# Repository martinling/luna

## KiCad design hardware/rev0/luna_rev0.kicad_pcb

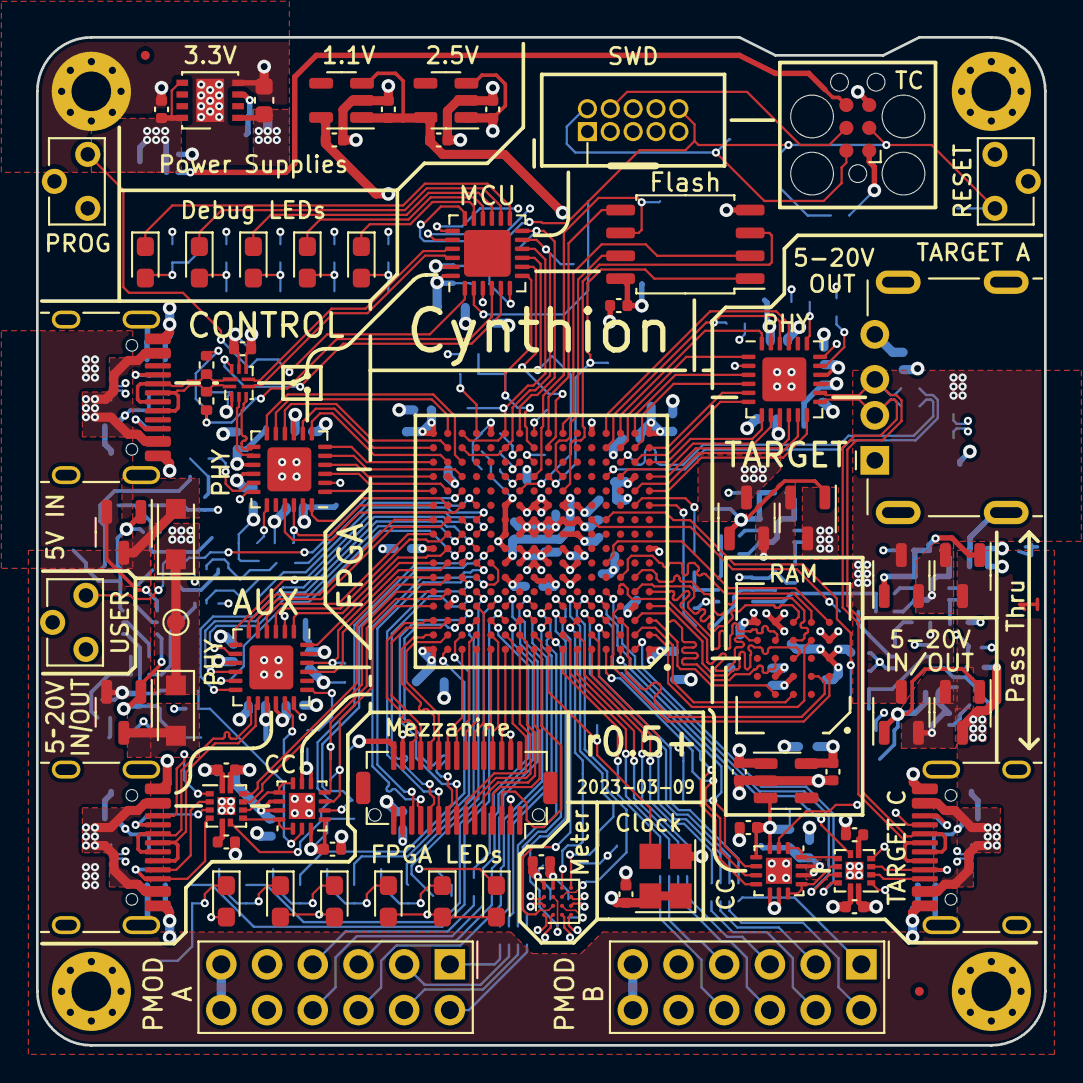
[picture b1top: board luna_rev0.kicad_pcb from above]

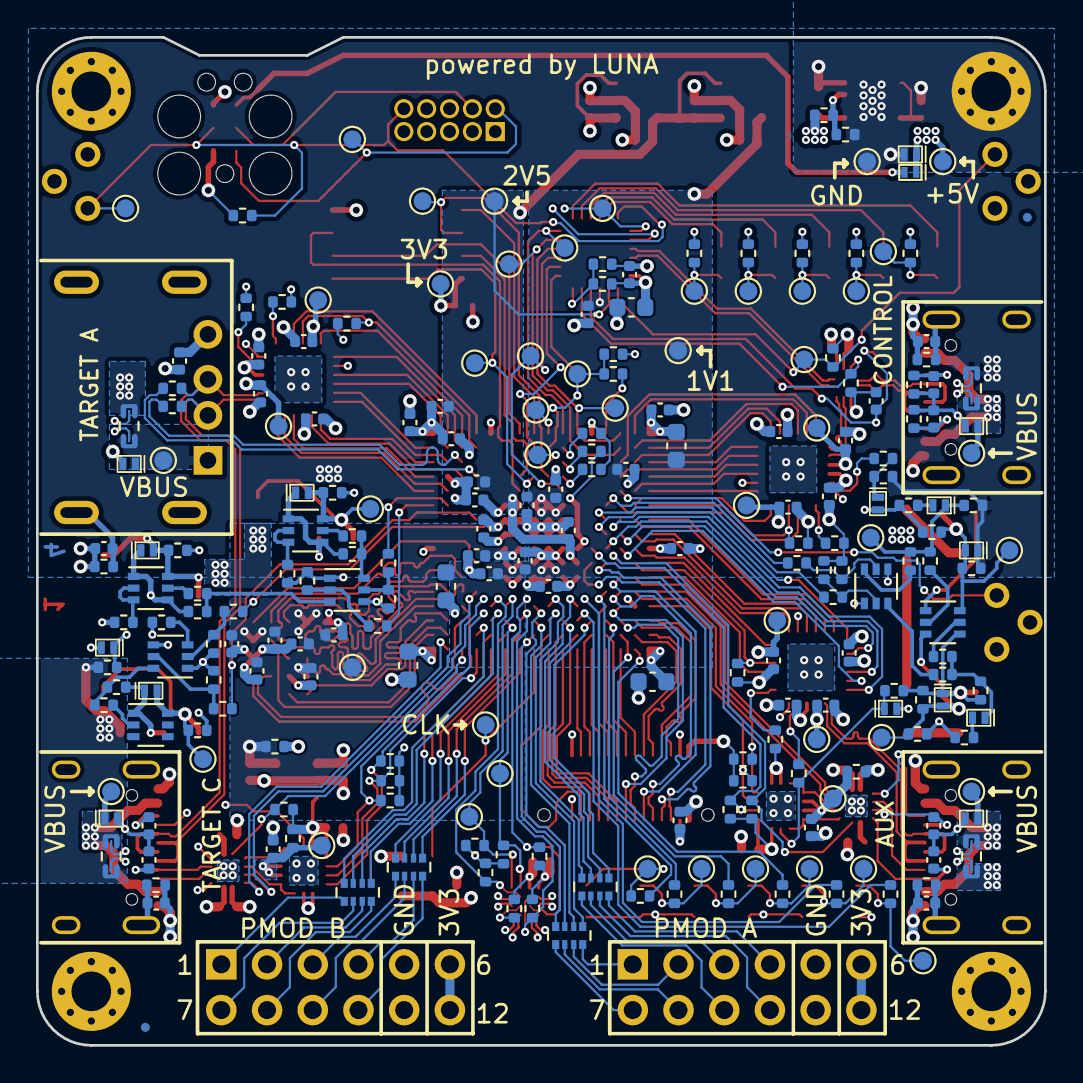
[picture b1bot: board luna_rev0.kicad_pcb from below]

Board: 4 copper layers, 56.0 x 56.0 mm, 313 parts (235 on the bottom side), 285 nets.

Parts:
C1, C2, C3, C4, C20, C73: 2.2uF; C_0603_1608Metric
C5, C6, C8, C13, C16, C17, C18, C19, C21, C22, C28, C29, C30, C34, C36, C37, C41, C42, C43, C48, C49, C50, C56, C58, C59, C60, C72, C74: 1uF; C_0402_1005Metric
C7, C9, C10, C11, C12, C14, C15, C23, C24, C26, C27, C31, C32, C33, C35, C38, C39, C40, C44, C45, C46, C51, C57, C61, C63, C64, C65, C66, C67, C68, C69, C70, C71: 0.1uF; C_0402_1005Metric
C25, C47, C52, C53, C54, C55: 390pF; C_0402_1005Metric
C62: 1nF; C_0402_1005Metric
D1, D8: D; D_SOD-123F
D2: RED; LED_0603_1608Metric_Pad1.05x0.95mm_HandSolder
D3: ORANGE; LED_0603_1608Metric_Pad1.05x0.95mm_HandSolder
D4: YELLOW; LED_0603_1608Metric_Pad1.05x0.95mm_HandSolder
D5: GREEN; LED_0603_1608Metric_Pad1.05x0.95mm_HandSolder
D6: BLUE; LED_0603_1608Metric_Pad1.05x0.95mm_HandSolder
D7: PURPLE; LED_0603_1608Metric_Pad1.05x0.95mm_HandSolder
D9: PMEG4010ESBYL; DSN1006-2
D10, D14: ICE BLUE; LED_0603_1608Metric_Pad1.05x0.95mm_HandSolder
D11, D13: PINK; LED_0603_1608Metric_Pad1.05x0.95mm_HandSolder
D12: WHITE; LED_0603_1608Metric_Pad1.05x0.95mm_HandSolder
D15, D18, D22: 24±2%; DFN1006-2
D16, D20: 18±2%; DFN1006-2
D17, D21: 5.6±2%; DFN1006-2
D19, D27, D28, D29: 6.2±2%; DFN1006-2
D23, D24, D25, D26: TVS; DFN1006-2
FID1, FID2, FID3, FID4: Fiducial; Fiducial_0.5mm_Mask1mm
H1, H2, H3, H4: MountingHole; MountingHole_2.2mm_M2_Pad_Via
IC1: ECP5-BGA256; lattice_cabga256
J1, J2, J4: USB_C_Receptacle_USB2.0; USB_C_Receptacle_HRO_TYPE-C-31-M-12
J3: USB_A; USB_A_Kycon_KUSBXHT-SB-AS1N-B30-NF_Horizontal
J5: MEZZANINE; Amphenol_10132798-03
J6: MCU_SWD; SWD_CONNECTOR_LARGE_BOX
J7: PMOD_A; PinSocket_2x06_P2.54mm_PMOD
J8: PMOD_B; PinSocket_2x06_P2.54mm_PMOD
J10: TC_SWD; Tag-Connect_TC2030-IDC-FP_2x03_P1.27mm_Vertical
Q1, Q2, Q4, Q5, Q6, Q7, Q9, Q12: PMOS; SOT-23-3
Q3, Q8, Q11: 2NPN; SOT-363_SC-70-6
Q10, Q13, Q14, Q15: 2PNP; SOT-363_SC-70-6
R1, R2, R42, R59: 0.02±1%; R_0603_1608Metric_Current_Sense
R3, R47, R48, R49, R60, R61, R69, R70, R76, R77: 33k; R_0402_1005Metric
R4, R32, R36, R43, R50, R51, R54, R102: 0; R_0402_1005Metric
R5, R8, R9, R10, R30, R31, R33, R38, R40, R63, R65, R71, R78, R83, R84, R88, R97, R98: 2.2k; R_0402_1005Metric
R6, R12, R13, R14, R15, R22, R23, R24, R25, R29, R37, R39, R41, R52, R53, R64, R66, R72, R79, R85, R86, R87, R89, R99, R100, R101: 10k; R_0402_1005Metric
R7, R11, R34, R35, R44, R45, R46: 5.1k; R_0402_1005Metric
R16, R18, R20: 8.06k±1%; R_0402_1005Metric
R17, R19, R21: 20k; R_0402_1005Metric
R26, R27, R28, R57, R58: 1k; R_0402_1005Metric
R55, R56, R68, R75: 820k; R_0402_1005Metric
R62, R90, R91, R92, R93, R94, R95, R96: 100k; R_0402_1005Metric
R67, R73, R74, R80, R82: 18.7k±1%; R_0402_1005Metric
R81: 58.3k±1%; R_0402_1005Metric
RN1, RN2, RN3, RN4: 33; R_Array_Convex_4x0402
SW1: BTN_PROGRAM; SW_Tactile_SPST_Angled_TC-1109DE-B-F
SW2: BTN_RESET; SW_Tactile_SPST_Angled_TC-1109DE-B-F
SW3: BTN_USER; SW_Tactile_SPST_Angled_TC-1109DE-B-F
TP1, TP2, TP3, TP4, TP5, TP6, TP7, TP8, TP9, TP10, TP11, TP12, TP13, TP14, TP15, TP16, TP17, TP18, TP19, TP20, TP21, TP22, TP23, TP24, TP26, TP27, TP28, TP29, TP30, TP31, TP32, TP34, TP35, TP36, TP37, TP38, TP39, TP40, TP41, TP42, TP43, TP44, TP46, TP47, TP49, TP50, TP51, TP52, TP53, TP54, TP55: TestPoint; TestPoint_Pad_D1.0mm
U1: PAC195X-1-WLCSP; WLCSP-16_2.225x2.170mm_Layout4x4_P0.5mm
U2, U12: FUSB302BMPX; WQFN-14-1EP_2.5x2.5mm_P0.5mm_EP1.45x1.45mm
U3: AP7361EA-33; DFN-8-1EP_3x3mm_P0.65mm_EP1.55x2.4mm
U4: TCR2EF115; SOT-23-5
U5: MIC5504-2.5YM5; SOT-23-5
U6: ATSAMD11; QFN-24-1EP_4x4mm_P0.5mm_EP2.6x2.6mm
U7: W25Q32JVSS; SOIC-8_5.23x5.23mm_P1.27mm
U8, U9, U11: USB3343-CP; VQFN-24-1EP_4x4mm_P0.5mm_EP2.45x2.45mm
U10: HyperRAM; BGA-24_5x5_6.0x8.0mm
U13, U14: DPO2036; Diodes_UQFN2020-12_Type-B
U15: MIC5504-1.8YM5; SOT-23-5
U16: PI3USB102G; Diodes_10-TQFN_ZL
Y1: Osc60MHz; Crystal_SMD_3225-4Pin_3.2x2.5mm

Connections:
+1V1: C1.1, C3.1, C7.1, C9.1, C11.1, C13.1, C15.1, C17.1, C29.1, IC1.G6 (VCC_1), IC1.G7 (VCC_2), IC1.G9 (VCC_3), IC1.L8 (VCC_4), IC1.L9 (VCC_5), IC1.L10 (VCC_6), TP4.1, U4.5 (VOUT), U6.3 (PA04)
+2V5: C22.1, C24.1, C26.1, C27.1, C30.1, IC1.G11 (VCCAUX_1), IC1.L7 (VCCAUX_2), TP5.1, U4.1 (VIN), U4.3 (EN), U5.5 (VOUT), U6.2 (PA03)
+3V3: C2.1, C4.1, C8.1, C10.1, C12.1, C14.1, C16.1, C18.1, C20.1, C23.1, C28.1, C33.1, C34.1, C35.1, C38.1, C39.1, C40.1, C41.1, C44.1, C46.1, C49.1, C56.1, C58.1, C59.1, C61.1, C66.1, C67.1, C72.1, C73.1, C74.1, D2.2 (A), D3.2 (A), D4.2 (A), D5.2 (A), D6.2 (A), D7.2 (A), IC1.F6 (VCCIO0_1), IC1.F7 (VCCIO0_2), IC1.F10 (VCCIO1_1), IC1.F11 (VCCIO1_2), IC1.H11 (VCCIO2_1), IC1.J6 (VCCIO6_1), IC1.J7 (VCCIO6_2), IC1.J11 (VCCIO2_2), IC1.K11 (VCCIO3_1), IC1.L6 (VCCIO8), IC1.L11 (VCCIO3_2), J5.15, J5.16, J6.1 (VTref), J7.6, J7.12, J8.6, J8.12, J10.1, R6.1, R7.1, R8.1, R9.1, R10.1, R11.1, R13.2, R25.1, R32.2, R33.1, R36.2, R37.1, R38.1, R39.1, R52.1, R54.1, R81.1, R83.1, R84.1, R85.1, R86.1, R87.1, R97.1, R98.1, R99.1, R100.1, R101.1, TP3.1, U1.A4 (VDD), U2.3 (VDD), U2.4 (VDD), U3.1 (OUT), U5.1 (VIN), U5.3 (EN), U6.24 (VDD), U7.8 (VCC), U8.2 (CLKOUT), U8.9 (VDDIO), U8.16 (VBAT), U8.18 (ID), U9.2 (CLKOUT), U9.9 (VDDIO), U9.16 (VBAT), U9.18 (ID), U11.2 (CLKOUT), U11.9 (VDDIO), U11.16 (VBAT), U11.18 (ID), U12.3 (VDD), U12.4 (VDD), U13.12 (VSYS), U14.12 (VSYS), U15.1 (VIN), U15.3 (EN), U16.9 (VCC), Y1.1 (EN), Y1.4 (VDD)
+5V: C6.1, D1.1 (K), D8.1 (K), D9.1 (K), D19.1 (K), TP30.1, TP49.1, U3.5 (EN), U3.8 (IN)
/AUX Port/AUX.CLK: IC1.F16 (PR14A), U11.21 (REFCLK/XI)
/AUX Port/AUX.DATA0: IC1.J16 (PR23A), U11.4 (DATA0)
/AUX Port/AUX.DATA1: IC1.K15 (PR23D), U11.5 (DATA1)
/AUX Port/AUX.DATA2: IC1.K16 (PR23C), U11.6 (DATA2)
/AUX Port/AUX.DATA3: IC1.J13 (PR17C), U11.7 (DATA3)
/AUX Port/AUX.DATA4: IC1.J14 (PR20C), U11.8 (DATA4)
/AUX Port/AUX.DATA5: IC1.H13 (PR17B), U11.10 (DATA5)
/AUX Port/AUX.DATA6: IC1.H14 (PR14D), U11.11 (DATA6)
/AUX Port/AUX.DATA7: IC1.K14 (PR20D), U11.12 (DATA7)
/AUX Port/AUX.DIR: IC1.H15 (PR20B), U11.1 (DIR)
/AUX Port/AUX.NXT: IC1.J15 (PR23B), U11.3 (NXT)
/AUX Port/AUX.STP: IC1.G16 (PR20A), U11.24 (STP)
/AUX Port/AUX.~RESET: IC1.G15 (PR14B), R24.1, U11.22 (RESET)
/AUX Port/AUX_CC1: C52.1, J1.A5 (CC1), U14.3 (CC1C)
/AUX Port/AUX_CC1S: U12.10 (CC1), U12.11 (CC1), U14.8 (CC1S)
/AUX Port/AUX_CC2: C53.1, J1.B5 (CC2), U14.4 (CC2C)
/AUX Port/AUX_CC2S: U12.1 (CC2), U12.14 (CC2), U14.7 (CC2S)
/AUX Port/AUX_D+: J1.A6 (D+), J1.B6 (D+), U11.14 (D+)
/AUX Port/AUX_D-: J1.A7 (D-), J1.B7 (D-), U11.13 (D-)
/AUX Port/AUX_PHY_1V8: C50.1, TP35.1, U11.23 (VDD18)
/AUX Port/AUX_SBU1: J1.A8 (SBU1), U14.2 (SBU2C)
/AUX Port/AUX_SBU1S: IC1.F15 (PR11C), U14.10 (SBU1S)
/AUX Port/AUX_SBU2: J1.B8 (SBU2), U14.1 (SBU1C)
/AUX Port/AUX_SBU2S: IC1.E16 (PR11D), U14.9 (SBU2S)
/AUX Port/AUX_SCL: IC1.D16 (PR8A), R38.2, U12.6 (SCL)
/AUX Port/AUX_SDA: IC1.E15 (PR8B), R33.2, U12.7 (SDA)
/AUX Port/AUX_VCONN: C51.1, R32.1, TP37.1, U12.12 (VCONN), U12.13 (VCONN)
/AUX Port/~AUX_FAULT: IC1.G14 (PR14C), R99.2, U14.6 (FAULTB)
/AUX Port/~AUX_INT: IC1.H12 (PR17A), R39.2, U12.5 (INT_N)
/CONTROL Port/CONTROL.CLK: IC1.L14 (PR32C), U8.21 (REFCLK/XI)
/CONTROL Port/CONTROL.DATA0: IC1.N16 (PR32A), U8.4 (DATA0)
/CONTROL Port/CONTROL.DATA1: IC1.N14 (PR35D), U8.5 (DATA1)
/CONTROL Port/CONTROL.DATA2: IC1.P16 (PR35A), U8.6 (DATA2)
/CONTROL Port/CONTROL.DATA3: IC1.P15 (PR32B), U8.7 (DATA3)
/CONTROL Port/CONTROL.DATA4: IC1.R16 (PR35B), U8.8 (DATA4)
/CONTROL Port/CONTROL.DATA5: IC1.R15 (PR38C), U8.10 (DATA5)
/CONTROL Port/CONTROL.DATA6: IC1.T15 (PR38D), U8.11 (DATA6)
/CONTROL Port/CONTROL.DATA7: IC1.P14 (PR38B), U8.12 (DATA7)
/CONTROL Port/CONTROL.DIR: IC1.M16 (PR26C), U8.1 (DIR)
/CONTROL Port/CONTROL.NXT: IC1.M15 (PR26D), U8.3 (NXT)
/CONTROL Port/CONTROL.STP: IC1.L15 (PR26B), U8.24 (STP)
/CONTROL Port/CONTROL.~RESET: IC1.L16 (PR26A), R22.1, U8.22 (RESET)
/CONTROL Port/CONTROL_CC1: C25.1, J2.A5 (CC1), R34.2
/CONTROL Port/CONTROL_CC2: C47.1, J2.B5 (CC2), R35.2
/CONTROL Port/CONTROL_D+: J2.A6 (D+), J2.B6 (D+), R56.2, U16.2 (D-)
/CONTROL Port/CONTROL_D-: J2.A7 (D-), J2.B7 (D-), R55.1, U16.1 (D+)
/CONTROL Port/CONTROL_FPGA_D+: U8.14 (D+), U16.4 (1D-)
/CONTROL Port/CONTROL_FPGA_D-: U8.13 (D-), U16.5 (1D+)
/CONTROL Port/CONTROL_MCU_D+: U6.22 (PA25), U16.6 (2D-)
/CONTROL Port/CONTROL_MCU_D-: U6.21 (PA24), U16.7 (2D+)
/CONTROL Port/CONTROL_PHY_1V8: C37.1, TP17.1, U8.23 (VDD18)
/CONTROL Port/CONTROL_RESET_DETECT: C62.1, R55.2, R56.1, U6.4 (PA05)
/CONTROL Port/CONTROL_SWITCH: R15.1, U6.5 (PA06), U16.10 (S)
/CONTROL Port/CONTROL_VBUS_CLAMPED: D22.1 (K), R17.1, R46.1
/CONTROL Port/~AUX_VBUS_IN_EN: IC1.L13 (PR29C), R78.2
/CONTROL Port/~BTN_USER: IC1.M14 (PR32D), SW3.1 (A)
/CONTROL Port/~CONTROL_VBUS_IN_EN: IC1.K13 (PR29A), R71.2
/CONTROL Port/~FPGA_SELF_PROGRAM: IC1.T13 (PR44B), R5.2
/Clock and Pmod/CLKIN_60MHZ: IC1.A8 (PT29B), TP1.1, Y1.3 (OUT)
/Clock and Pmod/TARGET_C.SBU1S: IC1.A2 (PT4A), U13.10 (SBU1S)
/Clock and Pmod/TARGET_C.SBU2S: IC1.E4 (PT9A), U13.9 (SBU2S)
/Clock and Pmod/TARGET_C.SCL: IC1.A4 (PT6B), R98.2, U2.6 (SCL)
/Clock and Pmod/TARGET_C.SDA: IC1.C4 (PT11A), R97.2, U2.7 (SDA)
/Clock and Pmod/TARGET_C.~FAULT: IC1.D4 (PT9B), R100.2, U13.6 (FAULTB)
/Clock and Pmod/TARGET_C.~INT: IC1.A3 (PT6A), R37.2, U2.5 (INT_N)
/Debugger and FPGA Configuration/D0: IC1.T8 (D0/PICO/PB11B), U7.5 (DI(IO0))
/Debugger and FPGA Configuration/D1: IC1.T7 (D1/PICO/PB11A), U7.2 (DO(IO1))
/Debugger and FPGA Configuration/D2: IC1.M7 (D2/PB9B), U7.3 (IO2)
/Debugger and FPGA Configuration/D3: IC1.N7 (D3/PB9A), U7.7 (IO3)
/Debugger and FPGA Configuration/FPGA_CFG0: IC1.N10 (CFG_0), R12.1
/Debugger and FPGA Configuration/FPGA_CFG1: IC1.P10 (CFG_1), R13.1
/Debugger and FPGA Configuration/FPGA_CFG2: IC1.R10 (CFG_2), R14.1
/Debugger and FPGA Configuration/FPGA_CONFIG_CLK: IC1.N9 (MCLK/SCLK/CCLK), TP10.1, U7.6 (CLK)
/Debugger and FPGA Configuration/FPGA_DONE: IC1.P9 (DONE), TP12.1
/Debugger and FPGA Configuration/FPGA_INT: IC1.R8 (SN/CSN/PB13A), U6.8 (PA09/XOUT)
/Debugger and FPGA Configuration/FPGA_TCK: IC1.T10 (TCK), TP21.1, U6.12 (PA15)
/Debugger and FPGA Configuration/FPGA_TDI: IC1.R11 (TDI), IC1.R14 (PR41B), TP24.1, U6.11 (PA14)
/Debugger and FPGA Configuration/FPGA_TDO: IC1.M10 (TDO), TP23.1, U6.9 (PA10)
/Debugger and FPGA Configuration/FPGA_TMS: IC1.T11 (TMS), IC1.T14 (PR41D), TP22.1, U6.10 (PA11)
/Debugger and FPGA Configuration/MCU_SWDCLK: J6.4 (SWDCLK/TCK), J10.4, TP19.1, U6.19 (PA30/SWCLK)
/Debugger and FPGA Configuration/MCU_SWDIO: J6.2 (SWDIO/TMS), J10.2, TP20.1, U6.20 (PA31/SWDIO)
/Debugger and FPGA Configuration/~BTN_PROGRAM: R101.2, SW1.1 (A), TP15.1, U6.1 (PA02)
/Debugger and FPGA Configuration/~BTN_RESET: J6.10 (~RESET), J10.3, R25.2, SW2.1 (A), TP18.1, U6.18 (PA28/~RST)
/Debugger and FPGA Configuration/~CS_DI: IC1.N8 (HOLDN/DI/PB15A), TP11.1, U7.1 (~CS)
/Debugger and FPGA Configuration/~FPGA_INIT: IC1.T9 (INITN), TP13.1
/Debugger and FPGA Configuration/~FPGA_PROGRAM: IC1.R9 (PROGRAMN), R5.1, R6.2, TP14.1, U6.7 (PA08/XIN)
/LEDs and Pmod/LED0: IC1.E13 (PT62B), R31.2
/LEDs and Pmod/LED1: IC1.C13 (PT60B), R30.2
/LEDs and Pmod/LED2: IC1.B14 (PT67A), R29.2
/LEDs and Pmod/LED3: IC1.A15 (PT67B), R28.2
/LEDs and Pmod/LED4: IC1.D12 (PT58A), R27.2
/LEDs and Pmod/LED5: IC1.C11 (PT49B), R26.2
/PMOD_A0: J7.1, RN1.8 (R1.2)
/PMOD_A1: J7.2, RN1.7 (R2.2)
/PMOD_A2: J7.3, RN2.6 (R3.2)
/PMOD_A3: J7.4, RN2.8 (R1.2)
/PMOD_A4: J7.7, RN1.5 (R4.2)
/PMOD_A5: J7.8, RN1.6 (R3.2)
/PMOD_A6: J7.9, RN2.5 (R4.2)
/PMOD_A7: J7.10, RN2.7 (R2.2)
/PMOD_B0: J8.1, RN4.5 (R4.2)
/PMOD_B1: J8.2, RN4.7 (R2.2)
/PMOD_B2: J8.3, RN3.5 (R4.2)
/PMOD_B3: J8.4, RN3.7 (R2.2)
/PMOD_B4: J8.7, RN4.6 (R3.2)
/PMOD_B5: J8.8, RN4.8 (R1.2)
/PMOD_B6: J8.9, RN3.6 (R3.2)
/PMOD_B7: J8.10, RN3.8 (R1.2)
/Power Distribution and Monitoring/ADDRSEL: R102.2, U1.C2 (ADDRSEL)
/Power Distribution and Monitoring/AUX_VBUS: D25.1 (K), J1.A4 (VBUS), J1.A9 (VBUS), J1.B4 (VBUS), J1.B9 (VBUS), R42.4, TP34.1
/Power Distribution and Monitoring/AUX_VBUS_EN: IC1.L2 (PL26B), R63.2
/Power Distribution and Monitoring/CONTROL_VBUS: D23.1 (K), J2.A4 (VBUS), J2.A9 (VBUS), J2.B4 (VBUS), J2.B9 (VBUS), R1.1, TP16.1
/Power Distribution and Monitoring/CONTROL_VBUS_EN: IC1.L1 (PL26A), R40.2
/Power Distribution and Monitoring/TARGET_A_DISCHARGE: IC1.K4 (PL29A), R88.2
/Power Distribution and Monitoring/TARGET_A_VBUS: D24.1 (K), J3.1 (VBUS), R2.4, TP7.1
/Power Distribution and Monitoring/TARGET_C_VBUS: D26.1 (K), J4.A4 (VBUS), J4.A9 (VBUS), J4.B4 (VBUS), J4.B9 (VBUS), R59.4, TP40.1
/Power Distribution and Monitoring/~TARGET_C_VBUS_EN: IC1.K5 (PL29B), R65.2
/RAM/RAM.CK: IC1.C3 (PL2C), U10.B2 (CK)
/RAM/RAM.DQ0: IC1.F2 (PL11C), U10.D3 (DQ0)
/RAM/RAM.DQ1: IC1.B1 (PL2A), U10.D2 (DQ1)
/RAM/RAM.DQ2: IC1.C2 (PL5B), U10.C4 (DQ2)
/RAM/RAM.DQ3: IC1.E1 (PL11D), U10.D4 (DQ3)
/RAM/RAM.DQ4: IC1.E3 (PL5C), U10.D5 (DQ4)
/RAM/RAM.DQ5: IC1.E2 (PL8B), U10.E3 (DQ5)
/RAM/RAM.DQ6: IC1.F3 (PL5D), U10.E2 (DQ6)
/RAM/RAM.DQ7: IC1.G4 (PL11B), U10.E1 (DQ7)
/RAM/RAM.RWDS: IC1.D1 (PL8A), U10.C3 (RWDS)
/RAM/RAM.~CK: IC1.D3 (PL2D), U10.B1 (~CK)
/RAM/RAM.~CS: IC1.B2 (PL2B), U10.A3 (~CS)
/RAM/RAM.~RESET: IC1.C1 (PL5A), U10.A4 (~RESET)
/TARGET Port/TARGET.CLK: IC1.T4 (PL44B), U9.21 (REFCLK/XI)
/TARGET Port/TARGET.DATA0: IC1.R2 (PL38C), U9.4 (DATA0)
/TARGET Port/TARGET.DATA1: IC1.R1 (PL35B), U9.5 (DATA1)
/TARGET Port/TARGET.DATA2: IC1.P2 (PL32B), U9.6 (DATA2)
/TARGET Port/TARGET.DATA3: IC1.P1 (PL35A), U9.7 (DATA3)
/TARGET Port/TARGET.DATA4: IC1.N3 (PL35D), U9.8 (DATA4)
/TARGET Port/TARGET.DATA5: IC1.N1 (PL32A), U9.10 (DATA5)
/TARGET Port/TARGET.DATA6: IC1.M2 (PL26D), U9.11 (DATA6)
/TARGET Port/TARGET.DATA7: IC1.M1 (PL26C), U9.12 (DATA7)
/TARGET Port/TARGET.DIR: IC1.R3 (PL41B), U9.1 (DIR)
/TARGET Port/TARGET.NXT: IC1.T2 (PL38D), U9.3 (NXT)
/TARGET Port/TARGET.STP: IC1.T3 (PL41D), U9.24 (STP)
/TARGET Port/TARGET.~RESET: IC1.R4 (PL41C), R23.1, U9.22 (RESET)
/TARGET Port/TARGET_CC1: C54.1, J4.A5 (CC1), U13.3 (CC1C)
/TARGET Port/TARGET_CC1S: U2.10 (CC1), U2.11 (CC1), U13.8 (CC1S)
/TARGET Port/TARGET_CC2: C55.1, J4.B5 (CC2), U13.4 (CC2C)
/TARGET Port/TARGET_CC2S: U2.1 (CC2), U2.14 (CC2), U13.7 (CC2S)
/TARGET Port/TARGET_D+: J3.3 (D+), J4.A6 (D+), J4.B6 (D+), R58.1, U9.14 (D+)
/TARGET Port/TARGET_D-: J3.2 (D-), J4.A7 (D-), J4.B7 (D-), R57.1, U9.13 (D-)
/TARGET Port/TARGET_FS_MONITOR_D+: IC1.N4 (PL38A), R58.2
/TARGET Port/TARGET_FS_MONITOR_D-: IC1.P3 (PL38B), R57.2
/TARGET Port/TARGET_PHY_1V8: C43.1, TP27.1, U9.23 (VDD18)
/TARGET Port/TARGET_SBU1: J4.A8 (SBU1), U13.1 (SBU1C)
/TARGET Port/TARGET_SBU2: J4.B8 (SBU2), U13.2 (SBU2C)
/TARGET Port/TARGET_VCONN: C45.1, R36.1, TP36.1, U2.12 (VCONN), U2.13 (VCONN)
AUX_SENSE+: R42.3, U1.A3 (SENSE1+)
AUX_SENSE-: R42.2, U1.A2 (SENSE1-)
AUX_VBUS_CLAMPED: D15.1 (K), R21.1, R44.1, U12.2 (VBUS)
AUX_VBUS_IN: D20.1 (K), Q4.3 (D), Q10.4 (E2), Q12.2 (S), R42.1, R44.2, R74.1, R75.1
CONTROL_SENSE+: R1.2, U1.A1 (SENSE2+)
CONTROL_SENSE-: R1.3, U1.B1 (SENSE2-)
CONTROL_VBUS_IN: D16.1 (K), Q1.3 (D), Q9.2 (S), Q10.1 (E1), R1.4, R46.2, R67.1, R68.1
GND: C1.2, C2.2, C3.2, C4.2, C5.2, C6.2, C7.2, C8.2, C9.2, C10.2, C11.2, C12.2, C13.2, C14.2, C15.2, C16.2, C17.2, C18.2, C19.2, C20.2, C21.2, C22.2, C23.2, C24.2, C25.2, C26.2, C27.2, C28.2, C29.2, C30.2, C31.2, C32.2, C33.2, C34.2, C35.2, C36.2, C37.2, C38.2, C39.2, C40.2, C41.2, C42.2, C43.2, C44.2, C45.2, C46.2, C47.2, C48.2, C49.2, C50.2, C51.2, C52.2, C53.2, C54.2, C55.2, C56.2, C57.2, C58.2, C59.2, C60.2, C61.2, C62.2, C63.2, C64.2, C65.2, C66.2, C67.2, C68.2, C69.1, C70.2, C71.1, C72.2, C73.2, C74.2, D15.2 (A), D18.2 (A), D19.2 (A), D22.2 (A), D23.2 (A), D24.2 (A), D25.2 (A), D26.2 (A), H1.1, H2.1, H3.1, H4.1, IC1.A1 (GND_1), IC1.A16 (GND_2), IC1.D2 (GND_3), IC1.D15 (GND_4), IC1.F8 (GND_5), IC1.F9 (GND_6), IC1.G8 (GND_7), IC1.G10 (GND_8), IC1.H1 (GND_9), IC1.H8 (GND_10), IC1.H9 (GND_11), IC1.H10 (GND_12), IC1.H16 (GND_13), IC1.J8 (GND_14), IC1.J9 (GND_15), IC1.J10 (GND_16), IC1.K6 (GND_17), IC1.K7 (GND_18), IC1.K8 (GND_19), IC1.K9 (GND_20), IC1.K10 (GND_21), IC1.N2 (GND_22), IC1.N15 (GND_23), IC1.T1 (GND_24), IC1.T5 (GND_25), IC1.T12 (GND_26), IC1.T16 (GND_27), J1.A1 (GND), J1.A12 (GND), J1.B1 (GND), J1.B12 (GND), J2.A1 (GND), J2.A12 (GND), J2.B1 (GND), J2.B12 (GND), J3.4 (GND), J4.A1 (GND), J4.A12 (GND), J4.B1 (GND), J4.B12 (GND), J5.2, J5.14, J5.17, J5.29, J6.3 (GND), J6.5 (GND), J6.9 (GNDDetect), J7.5, J7.11, J8.5, J8.11, J10.5, Q3.1 (E1), Q3.4 (E2), Q8.1 (E1), Q8.4 (E2), Q11.1 (E1), Q11.4 (E2), R4.1, R12.2, R14.2, R15.2, R16.1, R18.1, R20.1, R22.2, R23.2, R24.2, R34.1, R35.1, R41.2, R43.2, R50.1, R51.2, R53.2, R64.2, R66.2, R70.2, R72.2, R73.2, R77.2, R79.2, R80.2, R82.2, R89.2, R90.1, R91.1, R94.1, R95.1, R96.1, R102.1, SW1.2 (B), SW2.2 (B), SW3.2 (B), TP28.1, U1.B4 (GND), U2.8 (GND), U2.9 (GND), U2.15 (GND), U3.4 (GND), U3.9 (GND), U4.2 (GND), U5.2 (GND), U6.23 (GND), U7.4 (GND), U8.25 (GND), U9.25 (GND), U10.B3 (VSS), U10.C1 (VSSQ), U10.E5 (VSSQ), U11.25 (GND), U12.8 (GND), U12.9 (GND), U12.15 (GND), U13.11 (GND), U13.13 (GND), U14.11 (GND), U14.13 (GND), U15.2 (GND), U16.3 (GND), U16.8 (~OE), Y1.2 (GND)
MEZZANINE3: IC1.B9 (PT38A), J5.3
MEZZANINE4: IC1.A9 (PT42A), J5.4
MEZZANINE5: IC1.B10 (PT44A), J5.5
MEZZANINE6: IC1.A10 (PT42B), J5.6
MEZZANINE7: IC1.B11 (PT49A), J5.7
MEZZANINE22: IC1.A14 (PT65B), J5.22
MEZZANINE23: IC1.B13 (PT60A), J5.23
MEZZANINE24: IC1.A13 (PT65A), J5.24
MEZZANINE25: IC1.D13 (PT62A), J5.25
MEZZANINE26: IC1.A12 (PT53B), J5.26
MEZZANINE27: IC1.B12 (PT56A), J5.27
MEZZANINE28: IC1.A11 (PT53A), J5.28
MON.GPIO: IC1.D7 (PT24B), R86.2, U1.B2 (GPIO/~ALERT2)
MON.SCL: IC1.C6 (PT22A), R83.2, TP50.1, U1.C4 (SCL)
MON.SDA: IC1.D6 (PT20B), R84.2, TP51.1, U1.D4 (SDA)
MON.SLOW: IC1.D5 (PT13B), R85.2, U1.C3 (SLOW/~ALERT)
MON.~PWRDN: IC1.C7 (PT27A), R87.2, U1.B3 (~PWRDN)
unnamed: C36.1, TP26.1, U8.15 (VDD33)
unnamed: C42.1, TP9.1, U9.15 (VDD33)
unnamed: C48.1, TP2.1, U11.15 (VDD33)
unnamed: C57.1, U13.5 (CB)
unnamed: C63.1, U14.5 (CB)
unnamed: C68.1, J3.5 (Shield), R4.2
unnamed: C69.2, J1.S1 (SHIELD), R43.1
unnamed: C70.1, J4.S1 (SHIELD), R50.2
unnamed: C71.2, J2.S1 (SHIELD), R51.1
unnamed: D1.2 (A), Q12.3 (D)
unnamed: D2.1 (K), R26.1, TP43.1
unnamed: D3.1 (K), R27.1, TP47.1
unnamed: D4.1 (K), R28.1, TP52.1
unnamed: D5.1 (K), R29.1, TP53.1
unnamed: D6.1 (K), R30.1, TP54.1
unnamed: D7.1 (K), R31.1, TP55.1
unnamed: D8.2 (A), Q9.3 (D)
unnamed: D9.2 (A), J10.6
unnamed: D10.1 (K), U6.13 (PA16)
unnamed: D10.2 (A), R7.2, TP31.1
unnamed: D11.1 (K), U6.14 (PA17)
unnamed: D11.2 (A), R8.2, TP32.1
unnamed: D12.1 (K), U6.15 (PA22)
unnamed: D12.2 (A), R9.2, TP38.1
unnamed: D13.1 (K), U6.16 (PA23)
unnamed: D13.2 (A), R10.2, TP39.1
unnamed: D14.1 (K), U6.17 (PA27)
unnamed: D14.2 (A), R11.2, TP41.1
unnamed: D16.2 (A), Q9.1 (G), Q10.6 (C1), R68.2, R70.1, TP8.1
unnamed: D17.1 (K), R47.2, R67.2, R69.1, TP44.1
unnamed: D17.2 (A), R73.1
unnamed: D20.2 (A), Q10.3 (C2), Q12.1 (G), R75.2, R77.1, TP46.1
unnamed: D21.1 (K), R48.2, R74.2, R76.1
unnamed: D21.2 (A), R80.1
unnamed: D27.1 (K), Q1.2 (S), Q2.2 (S), Q13.1 (E1), Q13.4 (E2), R3.1
unnamed: D27.2 (A), Q1.1 (G), Q2.1 (G), Q13.6 (C1), R90.2, TP29.1
unnamed: D28.1 (K), Q4.2 (S), Q5.2 (S), Q14.1 (E1), Q14.4 (E2), R60.1
unnamed: D28.2 (A), Q4.1 (G), Q5.1 (G), Q14.6 (C1), R94.2
unnamed: D29.1 (K), Q6.2 (S), Q7.2 (S), Q15.1 (E1), R61.1
unnamed: D29.2 (A), Q6.1 (G), Q7.1 (G), Q15.6 (C1), R96.2, TP42.1
unnamed: IC1.A5 (PT18A), RN4.1 (R1.1)
unnamed: IC1.A6 (PT18B), RN3.3 (R3.1)
unnamed: IC1.A7 (PT29A), RN3.1 (R1.1)
unnamed: IC1.B4 (PT11B), RN4.4 (R4.1)
unnamed: IC1.B5 (PT15B), RN4.2 (R2.1)
unnamed: IC1.B6 (PT22B), RN3.4 (R4.1)
unnamed: IC1.B7 (PT27B), RN3.2 (R2.1)
unnamed: IC1.B8 (PT35B), RN1.4 (R4.1)
unnamed: IC1.B15 (PR2B), J5.21
unnamed: IC1.B16 (PR2A), J5.20
unnamed: IC1.C5 (PT15A), RN4.3 (R3.1)
unnamed: IC1.C8 (PT35A), RN1.2 (R2.1)
unnamed: IC1.C9 (PT38B), RN1.1 (R1.1)
unnamed: IC1.C10 (PT44B), RN2.2 (R2.1)
unnamed: IC1.C12 (PT56B), RN2.1 (R1.1)
unnamed: IC1.C14 (PR2C), J5.9
unnamed: IC1.C15 (PR5B), J5.19
unnamed: IC1.C16 (PR5A), J5.18
unnamed: IC1.D8 (PT33B), RN1.3 (R3.1)
unnamed: IC1.D9 (PT40A), RN2.4 (R4.1)
unnamed: IC1.D11 (PT51A), RN2.3 (R3.1)
unnamed: IC1.D14 (PR2D), J5.8
unnamed: IC1.E14 (PR5C), J5.11
unnamed: IC1.F14 (PR5D), J5.10
unnamed: IC1.G12 (PR11A), J5.13
unnamed: IC1.G13 (PR11B), J5.12
unnamed: Q3.2 (B1), R40.1, R41.1
unnamed: Q3.3 (C2), R60.2, R92.1
unnamed: Q3.5 (B2), R63.1, R64.1
unnamed: Q3.6 (C1), R3.2, R62.1
unnamed: Q8.2 (B1), R65.1, R66.1
unnamed: Q8.3 (C2), R49.2
unnamed: Q8.5 (B2), R88.1, R89.1
unnamed: Q8.6 (C1), R61.2, R93.1
unnamed: Q10.2 (B1), R47.1
unnamed: Q10.5 (B2), R48.1
unnamed: Q11.2 (B1), R71.1, R72.1
unnamed: Q11.3 (C2), R76.2
unnamed: Q11.5 (B2), R78.1, R79.1
unnamed: Q11.6 (C1), R69.2
unnamed: Q13.2 (B1), Q13.3 (C2), R91.2
unnamed: Q13.5 (B2), R62.2
unnamed: Q14.2 (B1), Q14.3 (C2), R95.2
unnamed: Q14.5 (B2), R92.2
unnamed: Q15.2 (B1), R93.2
unnamed: R16.2, U8.19 (RBIAS)
unnamed: R17.2, U8.17 (VBUS)
unnamed: R18.2, U9.19 (RBIAS)
unnamed: R19.2, U9.17 (VBUS)
unnamed: R20.2, U11.19 (RBIAS)
unnamed: R21.2, U11.17 (VBUS)
unnamed: R52.2, R53.1, U6.6 (PA07)
unnamed: R81.2, R82.1, U3.3 (ADJ/NC)
TARGET_A_SENSE+: R2.3, U1.D1 (SENSE3+)
TARGET_A_SENSE-: R2.2, U1.C1 (SENSE3-)
TARGET_A_VBUS_IN: Q2.3 (D), Q5.3 (D), Q6.3 (D), R2.1, R49.1
TARGET_C_SENSE+: R59.3, U1.D3 (SENSE4+)
TARGET_C_SENSE-: R59.2, U1.D2 (SENSE4-)
TARGET_C_VBUS_CLAMPED: D18.1 (K), R19.1, R45.1, U2.2 (VBUS)
TARGET_C_VBUS_IN: Q7.3 (D), R45.2, R59.1
VCCRAM: C5.1, C19.1, C21.1, C31.1, C32.1, C60.1, C64.1, C65.1, IC1.H6 (VCCIO7_1), IC1.H7 (VCCIO7_2), R54.2, TP6.1, U10.B4 (VCC), U10.D1 (VCCQ), U10.E4 (VCCQ), U15.5 (VOUT)

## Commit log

2022-01-24 Use async libusb1 for capture, libhackrf style.
2023-03-10 Back off AUX_VBUS_IN polygon from sensitive areas.
2023-03-10 Add additional silkscreen markings to front side.
2023-03-11 Second pass at silkscreen.
2023-06-26 Make clock generation optional for USBAnalyzerApplet.
2023-06-26 Make clock domain generation optional for speed test applets.
2023-06-27 Simplify logic for maintaining FIFO count.
2023-06-27 Don't discard data while in overrun state.
2023-06-28 Flush endpoint when analyzer overruns.
2023-06-28 Use a packet length of 0xFFFF to indicate an overrun event.
2023-06-28 After overrun, resume capture once FIFO is cleared.
2023-08-05 Remove platform definitions.
    Platform definitions will now be kept in separate repositories.
    Auto-detection will be used if the apollo_fpga module is present, and
    the detected Apollo device is supported by the installed 'cynthion' or
    'luna_boards' modules.
    In all other cases, the LUNA_PLATFORM environment variable must be set
    for get_appropriate_platform() to return a platform.
2023-08-07 Use a counter for USBInSpeedTestDevice payload
2023-08-07 Support alternative PID for speed test device.
2023-09-27 gateware: do not use Pin as a value
    Pin.eq() shall be avoided. Use internal signals instead.
2023-09-27 fix missing import
2023-09-27 I2CBusDriver: support output-only SCL line
2023-09-27 port I2CInitiator to Amaranth HDL
2023-09-27 wip: first i2c test for cynthion r1
2023-09-27 I2CDeviceInterface: avoid block if dev not present
2023-09-27 wip: initial i2c device interface
2023-09-27 I2CDeviceInitiator: reduce logic for internal regs
2023-09-27 gateware.architecture.adv: add ApolloAdvertiser
    This module uses the FPGA_INT line present in recent Cynthion boards as
    a one-way communication channel. Messages or "advertisements" are sent
    periodically.
    In this commit, it will announce its intention to acquire the main USB
    port (CONTROL). Apollo can choose to honor this request and keep the
    port handed off to the FPGA until these messages stop, which is
2023-09-27 Allow overriding the PHY for FlashBridge.
2023-09-27 honor_fpga_adv: force device enumeration after programming the FPGA
2023-09-27 applets: add configuration flash bridge
    This is an interface bridge between USB and the SPI bus wired to the
    configuration memory.
2023-09-27 I2CDeviceInterface: update FSM
2023-09-27 interactive-test: update i2c tests
2023-09-27 I2DeviceInterface: use repeated start when reading
2023-09-27 Support alternative VID for speed test device.
2023-09-27 Enable advertising for speed test devices on CONTROL port.
2023-09-27 wip: block writes/reads
    add ability to perform multi-byte writes and reads
2023-09-27 I2CDeviceInterface: fix writes
2023-09-27 Add VBUS enable registers to self-test.
2023-09-27 I2CDeviceInterface: simplify FSM
2023-09-27 i2c: merge in a single file
2023-10-09 USBDevice: call hooks specified in platform definition.
2023-10-09 Provide names to ClockDomain constructor calls.
2023-10-12 Write to analyzer buffer from sync clock domain.
    - The memory write port is now in the 'sync' clock domain (120MHz).
    - The analyzer FSM no longer drives the ring buffer write port directly.
    Instead, it sets 'write_packet' and 'write_header' signals to trigger
    the necessary memory operations.
    - A new FSM in the 'sync' domain handles these signals, and sets up
    the necessary writes to memory.
2023-10-12 analyzer: fix buffer writes
    Writes were not triggered when a byte arrived, but every cycle of the
    usb domain. This also caused headers to never be written.
2023-10-12 WIP memory-space read/writes
2023-10-12 hyperram_diagnostic: Amaranth RFC-2 compliance.
2023-10-12 analyzer: convert to 16-bit wide memory
2023-10-12 gateware.interface.psram: rename new_data_ready to read_ready
    This fits better with `write_ready` and makes it more similar to
    FIFOInterface signals.
2023-10-12 analyzer: first working version with integrated HyperRAM
2023-10-12 WIP enable burst reads
2023-10-12 gateware.interface.psram: enable burst writes
2023-10-12 gateware.interface.psram: re-organise command/address generation
2023-10-12 analyzer: write whole packets, decouple reads from capture FSM
2023-10-12 gateware.interface.psram: add write_ready signal
2023-10-12 hyperram_speed_test: add applet
2023-10-12 gateware.applets.hyperram_diagnostic: add a FIFO for reads/writes
2023-10-12 WIP DDRX1 HyperRAM interface
2023-10-16 Hardwire analyzer to capture continuously with no uplink.
2023-11-30 Write timestamp to analyzer stream.
2023-12-07 Precompute next event/header location after each packet byte.
2023-12-11 Write events to stream when timestamp counter is about to wrap.

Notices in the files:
hardware/rev0/luna_rev0.kicad_pcb:
Copyright 2019-2023 Great Scott Gadgets
Licensed under the CERN-OHL-P v2
